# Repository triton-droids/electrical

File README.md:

# electrical

### Inrush Current Limiting Board 
1/17/2026 - Added PDB V1 MAIN 2: Tae's final prototype of the Inrush Current Limiting Board

#### Note: 
Test PDB V1 11:8.kicad_sch conflicts with windows since it has a colon in it. This will probably cause some merge conflicts.

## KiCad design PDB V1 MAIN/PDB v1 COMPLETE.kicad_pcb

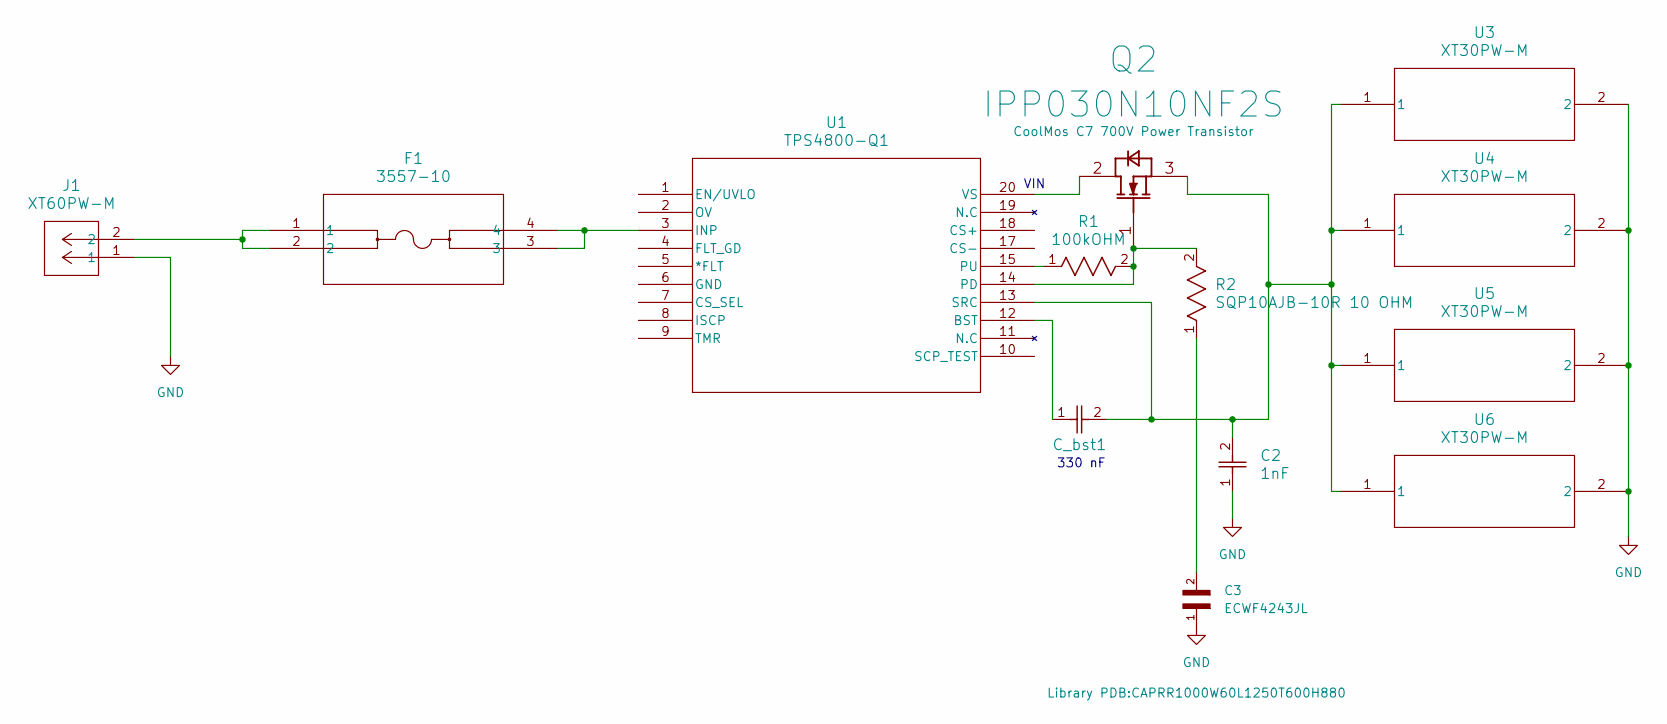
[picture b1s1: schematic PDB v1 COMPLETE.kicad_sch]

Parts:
C2: 1nF; CAP_16 X 25_PAN
C3: ECWF4243JL; CAPRR1000W60L1250T600H880; PARTREV 11-Oct-17
C_bst1: GRM32ER60G337ME05L; CAP_GRM32E_MUR
F1: 3557-10; 3557-10_KEY
J1: XT60PW-M; CONN_1805375_RSP
Q2: IPP030N10NF2S; IFX-PG-TO220-3-60
R1: 100kOHM; RN60_VIS
R2: SQP10AJB-10R 10 OHM; YAG_SQP10_YAG
U1: TPS4800-Q1; VSSOP19-DGX_TEX
U3, U4, U5, U6: XT30PW-M; XT30PW-M_AMA

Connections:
GND: C2.1, C3.1, J1.1, U3.2, U4.2, U5.2, U6.2
unnamed: C3.2, R2.1
unnamed: F1.1, F1.2, J1.2
unnamed: Q2.2 (DRAIN), U1.20 (VS)
unnamed: Q2.1 (GATE), R1.2, R2.2, U1.14 (PD)
unnamed: C2.2, C_bst1.2, Q2.3 (SOURCE), U1.13 (SRC), U3.1, U4.1, U5.1, U6.1
unnamed: C_bst1.1, U1.12 (BST)
unnamed: F1.3, F1.4, U1.3 (INP)
unnamed: R1.1, U1.15 (PU)

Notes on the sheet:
330 nF
VIN

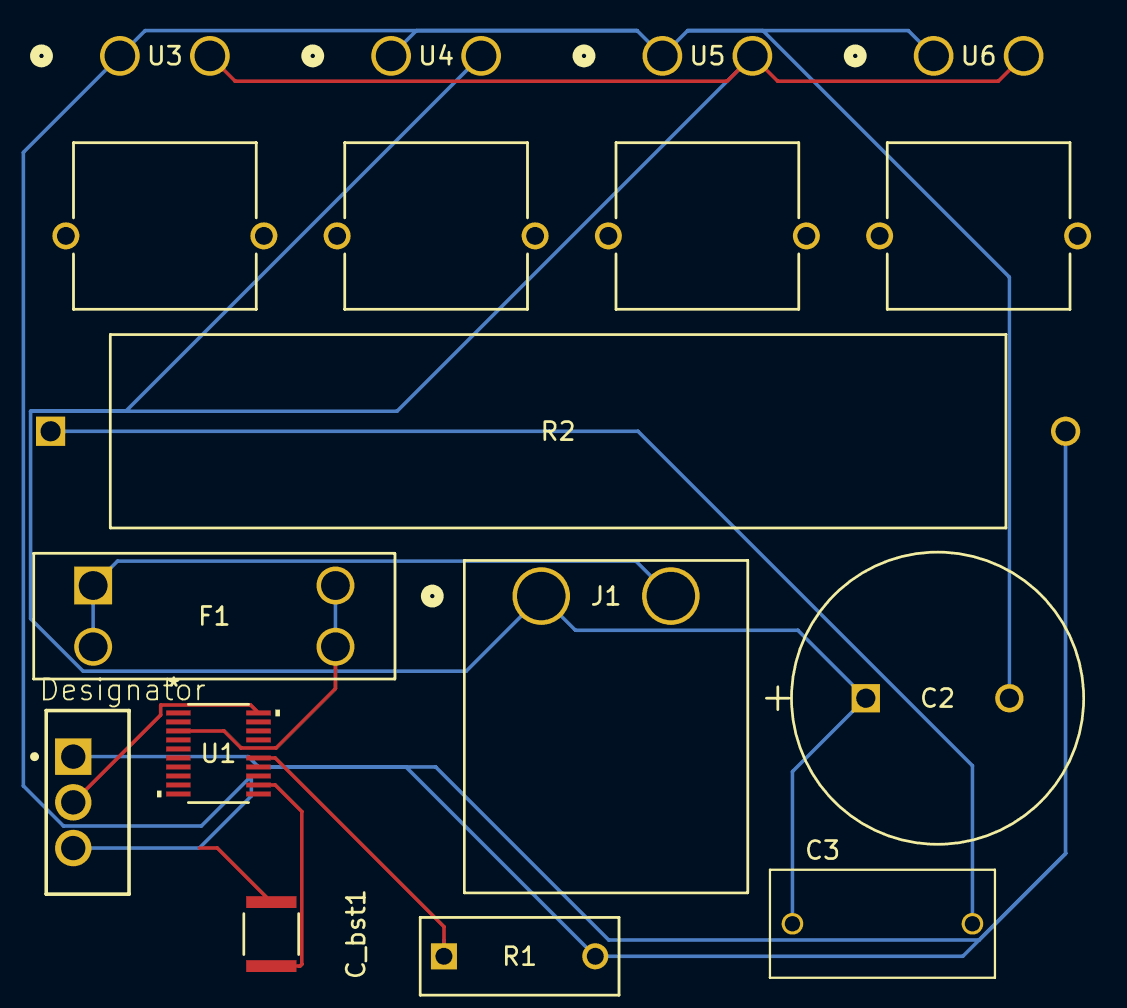
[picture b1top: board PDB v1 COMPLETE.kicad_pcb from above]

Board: 2 copper layers, 13 parts (0 on the bottom side), 9 nets.

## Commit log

2025-10-26 Initial Commit
    Base Temp File
2025-11-01 Create fuse
2025-11-01 Create hotswapic
2025-11-01 Create xt60
2025-11-02 Create xt30-M
2025-11-02 Update xt60
2025-11-09 Schematic for 11/8
2025-11-09 11/8 Final Commit of the Day
    We finished the base schematic just need to upload a fuse and an NMOS part and we are good to go.
2025-11-09 Create fuse+fuseholder
2025-11-15 Main Folder
    I created the main folder to fix our github integration.
2025-11-21 Pushing Last Weeks Changes/ Testing New Git Integration
    I am pushing the previous weeks changes while testing out git for KiCad.
2026-01-18 Added PDB V1 MAIN 2 project files to the repo. This should be the final prototype of the Inrush Current Limiting Board.
2026-01-18 Added PDB V1 MAIN 2 files to the repo. This represents the latest version of the Inrush Current Limiting Board.
2026-01-19 Add IMU Firmware
2026-02-08 upload arctos wrapper
